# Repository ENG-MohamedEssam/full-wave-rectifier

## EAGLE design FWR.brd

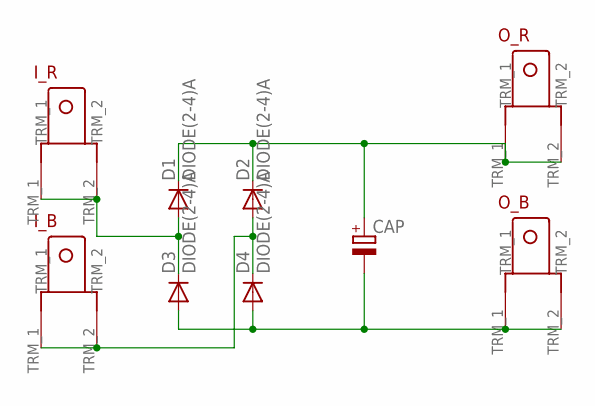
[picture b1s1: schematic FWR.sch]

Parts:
CAP: CAP_POL; E3,5-8
D1, D2, D3, D4: DIODE(2-4)A; DO35-10
I_B: TERMINAL_EDITED
I_R: TERMINAL_EDITED
O_B: TERMINAL_EDITED
O_R: TERMINAL_EDITED

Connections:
D1: CAP.+, D1.C, D2.C, O_R.TRM_1, O_R.TRM_2
unnamed: D2.A, D4.C, I_B.TRM_1, I_B.TRM_2
unnamed: D1.A, D3.C, I_R.TRM_1, I_R.TRM_2
unnamed: CAP.-, D3.A, D4.A, O_B.TRM_1, O_B.TRM_2

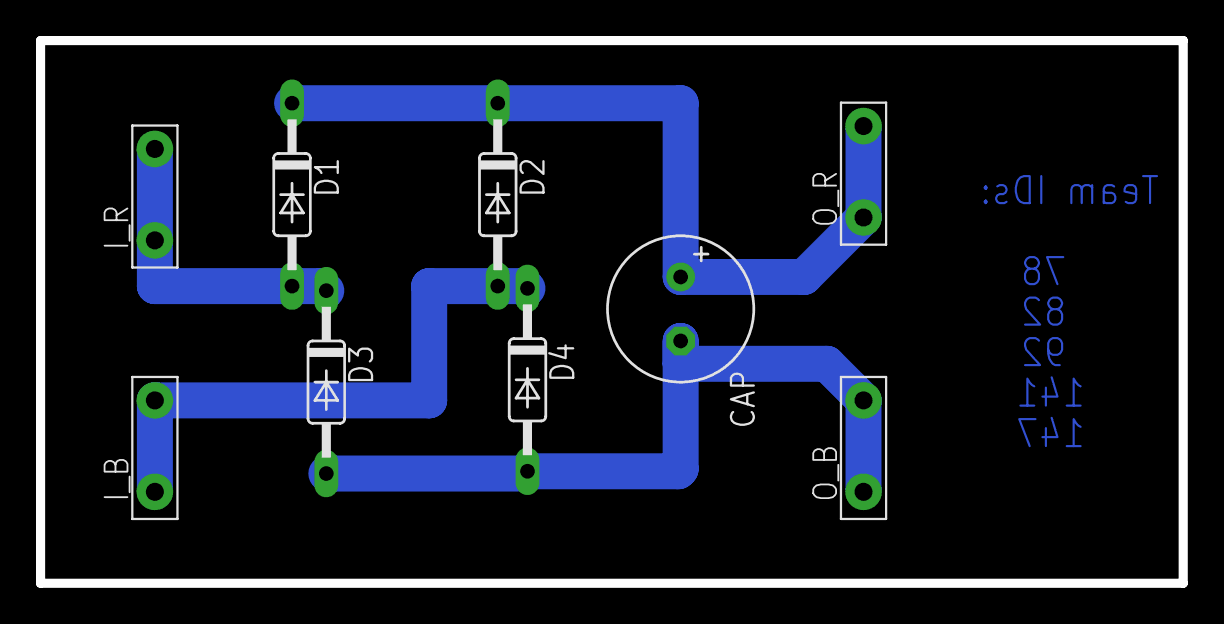
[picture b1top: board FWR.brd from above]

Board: 2 copper layers, 63.5 x 30.1 mm, 9 parts (0 on the bottom side), 4 nets.
